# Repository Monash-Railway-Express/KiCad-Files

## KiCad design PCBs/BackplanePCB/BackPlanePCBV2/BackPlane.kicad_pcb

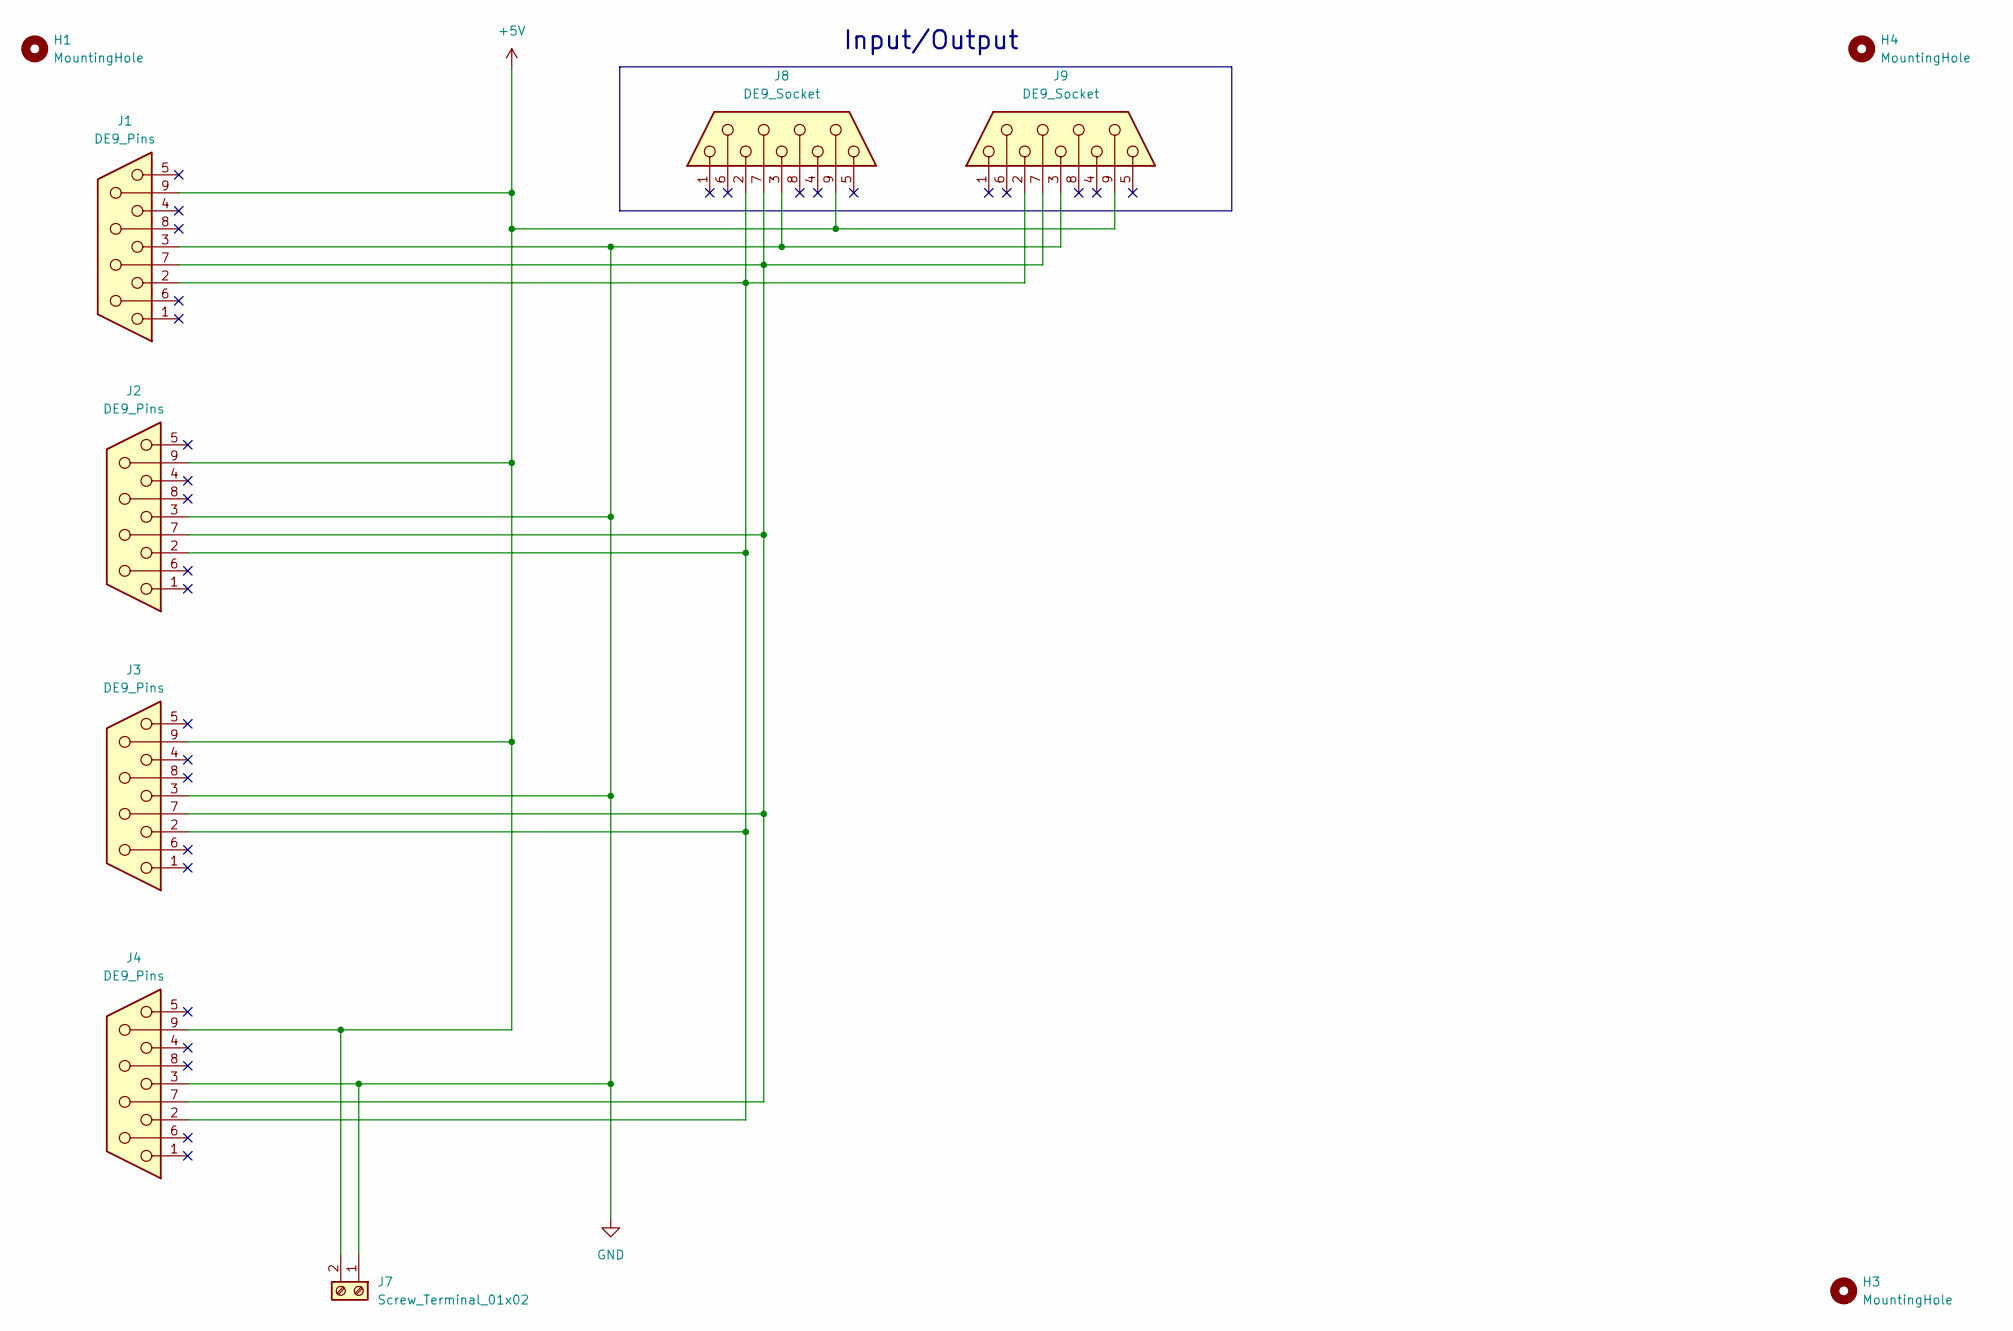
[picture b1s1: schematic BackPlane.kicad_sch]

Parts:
H1, H3, H4: MountingHole; MountingHole_5.3mm_M5_ISO14580
J1, J2, J3, J4: DE9_Pins; DSUB-9_Socket_Vertical_P2.77x2.84mm_MountingHoles
J7: Screw_Terminal_01x02; TerminalBlock_TE_282834-2_1x02_P2.54mm_Horizontal
J8, J9: DE9_Socket; CONN_2301844-1_TEC

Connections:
+5V: J1.9, J2.9, J3.9, J4.9, J7.2, J8.9, J9.9
GND: J1.3, J2.3, J3.3, J4.3, J7.1, J8.3, J9.3
unnamed: J1.2, J2.2, J3.2, J4.2, J8.2, J9.2
unnamed: J1.7, J2.7, J3.7, J4.7, J8.7, J9.7

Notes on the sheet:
Input/Output

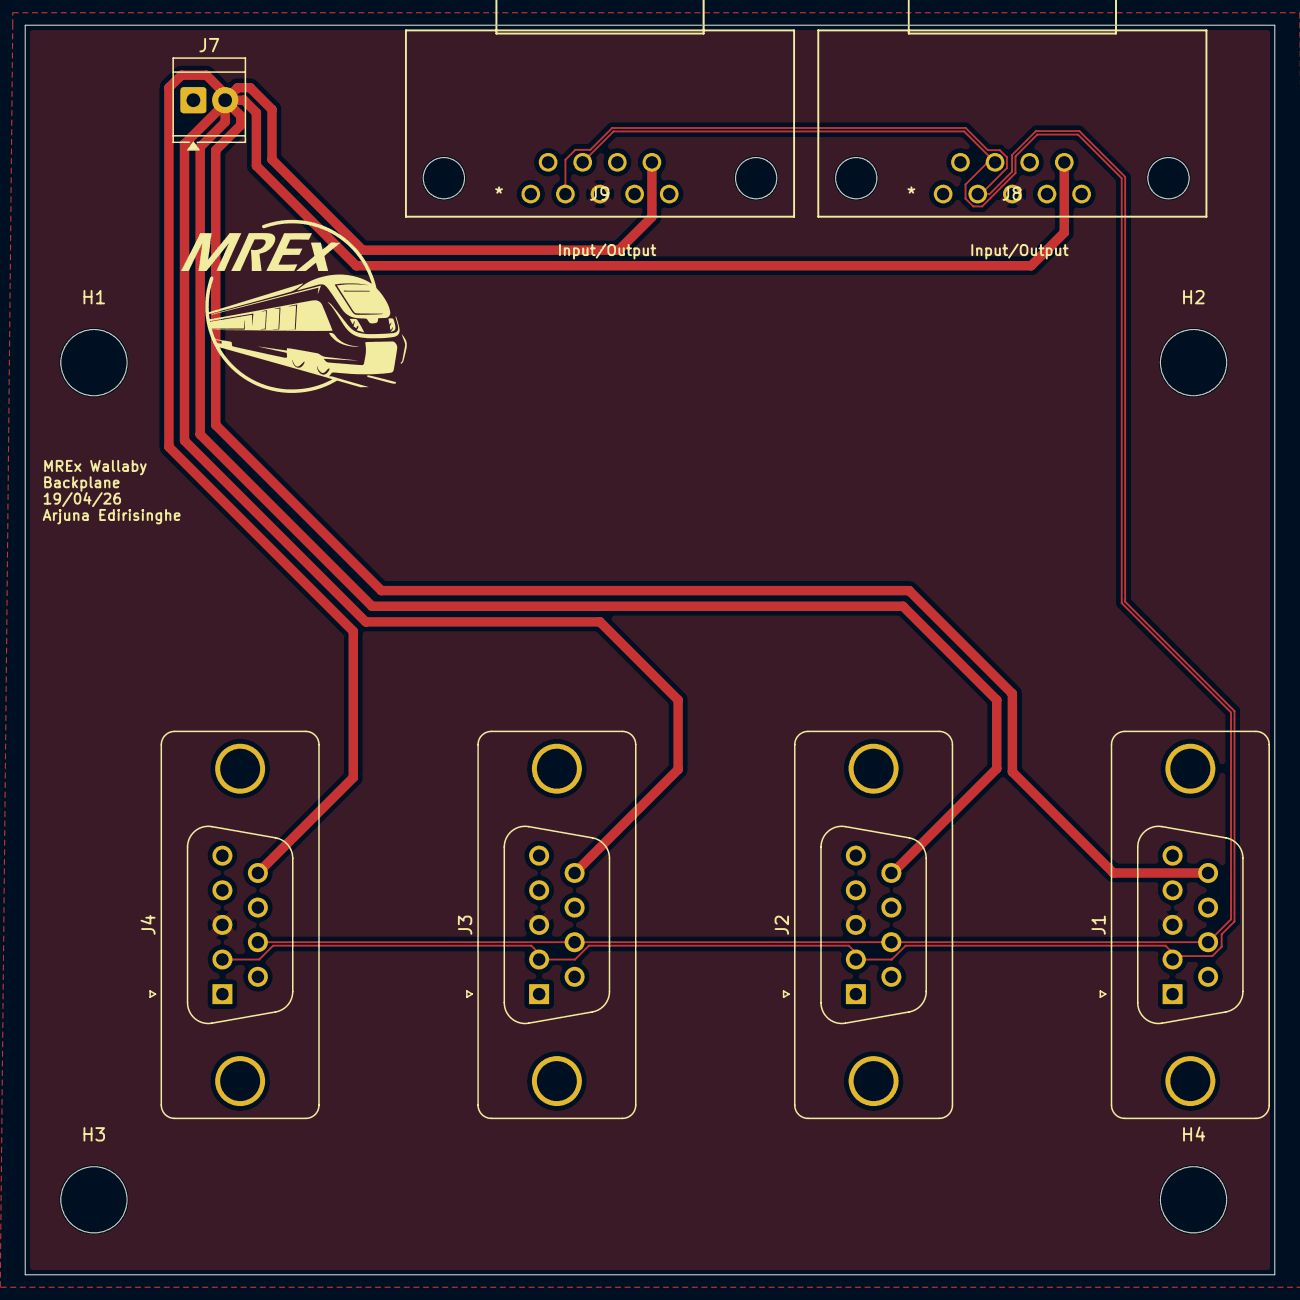
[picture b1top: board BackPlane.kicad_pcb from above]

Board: 2 copper layers, 100.0 x 100.0 mm, 11 parts (0 on the bottom side), 4 nets.

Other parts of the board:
H2: MountingHole; MountingHole_5.3mm_M5_ISO14580

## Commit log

2026-04-23 Backplane V2
    Added Backplane V2 Kicad project including Gerber files to repo. V2 has
    - pinouts adhering to PCB standards
    - power to all DB9 connectors
    - 1 less connector
